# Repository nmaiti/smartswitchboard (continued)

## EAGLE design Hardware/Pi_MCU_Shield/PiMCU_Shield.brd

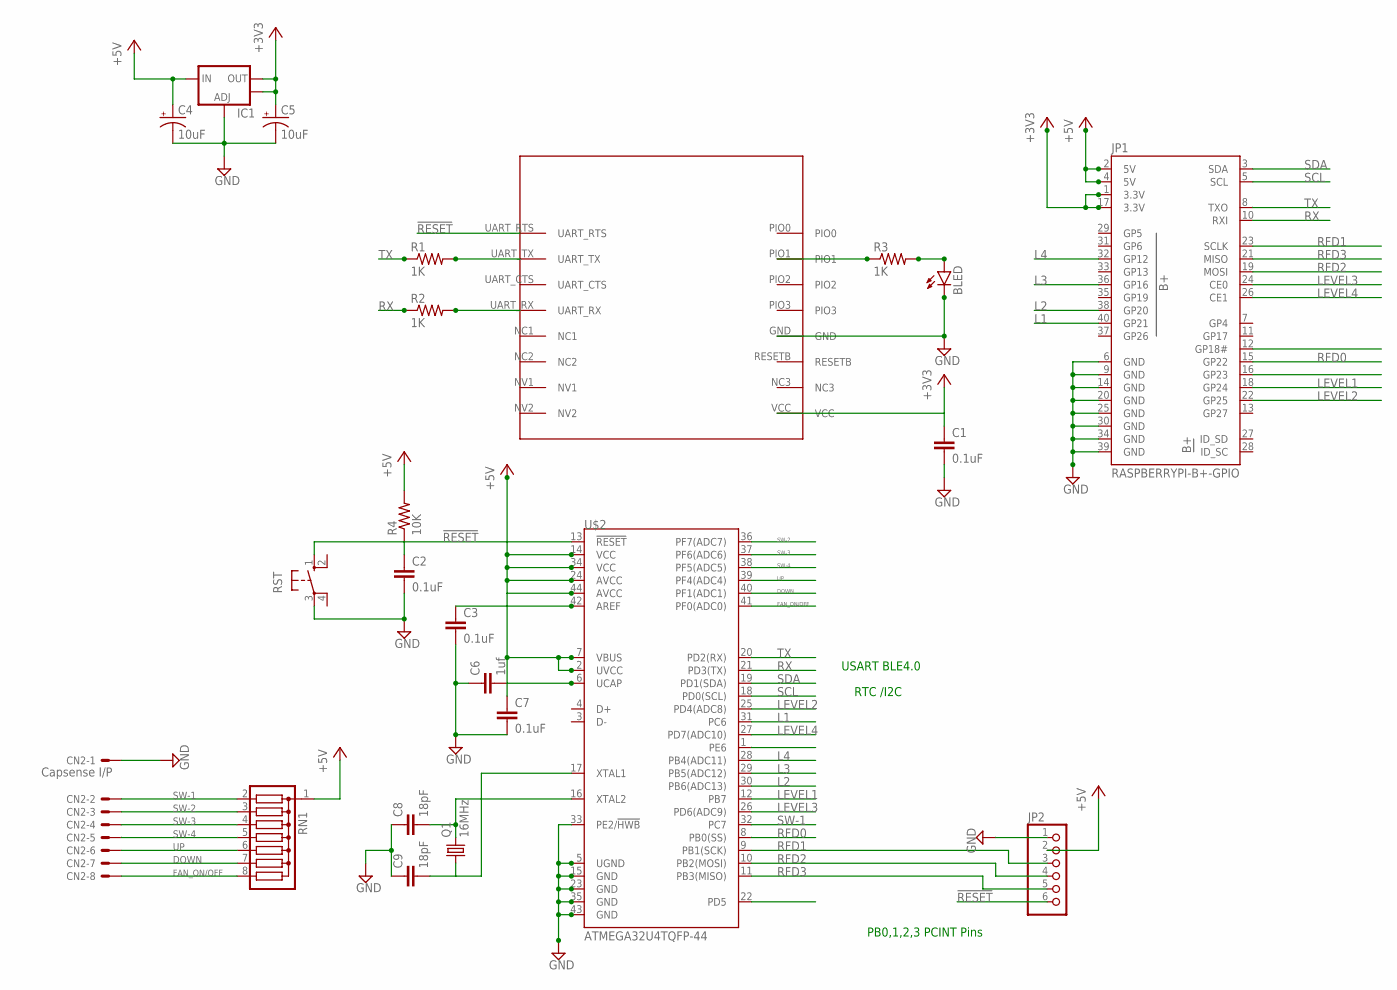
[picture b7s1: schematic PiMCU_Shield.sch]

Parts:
BLED: LED1206; LED-1206
C1, C2, C3, C7: 0.1uF; 1206
C4, C5: 10uF; EIA3216
C6: 1uf; 1206
C8, C9: 18pF; 1206
CN2: Capsense I/P; 22-23-2081
IC1: V_REG_LM1117SOT223; SOT223
JP1: RASPBERRYPI-B+-GPIO; 2X20-SHROUDED
JP2: PINHD-1X6; 1X06
Q1: 16MHz; HC49UP
R1, R2, R3: 1K; 1206
R4: 10K; 1206
RN1: G07R; SIL8
RST: 10-XX; B3F-10XX
U$1: HM-11
U$2: ATMEGA32U4TQFP-44; TQFP44

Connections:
!RESET: C2.1, JP2.6, R4.1, RST.1 (S), U$1.UART_RTS, U$2.13 (!RESET)
+3V3: C1.1, C5.A (+), IC1.2 (OUT), IC1.4 (OUT), JP1.1 (3.3V), JP1.17 (3.3V), U$1.VCC
+5V: C4.A (+), C7.1, IC1.3 (IN), JP1.2 (5V), JP1.4 (5V), JP2.2, R4.2, RN1.1, U$2.2 (UVCC), U$2.7 (VBUS), U$2.14 (VCC), U$2.24 (AVCC), U$2.34 (VCC), U$2.44 (AVCC)
DOWN: CN2.7, RN1.7, U$2.40 (PF1(ADC1))
FAN_ON/OFF: CN2.8, RN1.8, U$2.41 (PF0(ADC0))
GND: BLED.C, C1.2, C2.2, C3.2, C4.C (-), C5.C (-), C6.1, C7.2, C8.1, C9.1, CN2.1, IC1.1 (ADJ), JP1.6 (GND), JP1.9 (GND), JP1.14 (GND), JP1.20 (GND), JP1.25 (GND), JP1.30 (GND), JP1.34 (GND), JP1.39 (GND), JP2.1, RST.3, U$1.GND, U$2.5 (UGND), U$2.15 (GND), U$2.23 (GND), U$2.33 (PE2/!HWB), U$2.35 (GND), U$2.43 (GND)
L1: JP1.40 (GP21), U$2.31 (PC6)
L2: JP1.38 (GP20), U$2.30 (PB6(ADC13))
L3: JP1.36 (GP16), U$2.29 (PB5(ADC12))
L4: JP1.32 (GP12), U$2.28 (PB4(ADC11))
LEVEL1: JP1.18 (GP24), U$2.12 (PB7)
LEVEL2: JP1.22 (GP25), U$2.25 (PD4(ADC8))
LEVEL3: JP1.24 (CE0), U$2.26 (PD6(ADC9))
LEVEL4: JP1.26 (CE1), U$2.27 (PD7(ADC10))
unnamed: R1.2, U$1.UART_TX
unnamed: R2.2, U$1.UART_RX
unnamed: R3.1, U$1.PIO1
unnamed: BLED.A, R3.2
unnamed: C3.1, U$2.42 (AREF)
unnamed: C6.2, U$2.6 (UCAP)
unnamed: C8.2, Q1.2, U$2.16 (XTAL2)
unnamed: C9.2, Q1.1, U$2.17 (XTAL1)
RFD0: JP1.15 (GP22), U$2.8 (PB0(SS))
RFD1: JP1.23 (SCLK), JP2.3, U$2.9 (PB1(SCK))
RFD2: JP1.19 (MOSI), JP2.4, U$2.10 (PB2(MOSI))
RFD3: JP1.21 (MISO), JP2.5, U$2.11 (PB3(MISO))
RX: JP1.10 (RXI), R2.1, U$2.21 (PD3(TX))
SCL: JP1.5 (SCL), U$2.18 (PD0(SCL))
SDA: JP1.3 (SDA), U$2.19 (PD1(SDA))
SW-1: CN2.2, RN1.2, U$2.32 (PC7)
SW-2: CN2.3, RN1.3, U$2.36 (PF7(ADC7))
SW-3: CN2.4, RN1.4, U$2.37 (PF6(ADC6))
SW-4: CN2.5, RN1.5, U$2.38 (PF5(ADC5))
TX: JP1.8 (TXO), R1.1, U$2.20 (PD2(RX))
UP: CN2.6, RN1.6, U$2.39 (PF4(ADC4))

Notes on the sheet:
PB0,1,2,3 PCINT Pins
USART BLE4.0
RTC /I2C

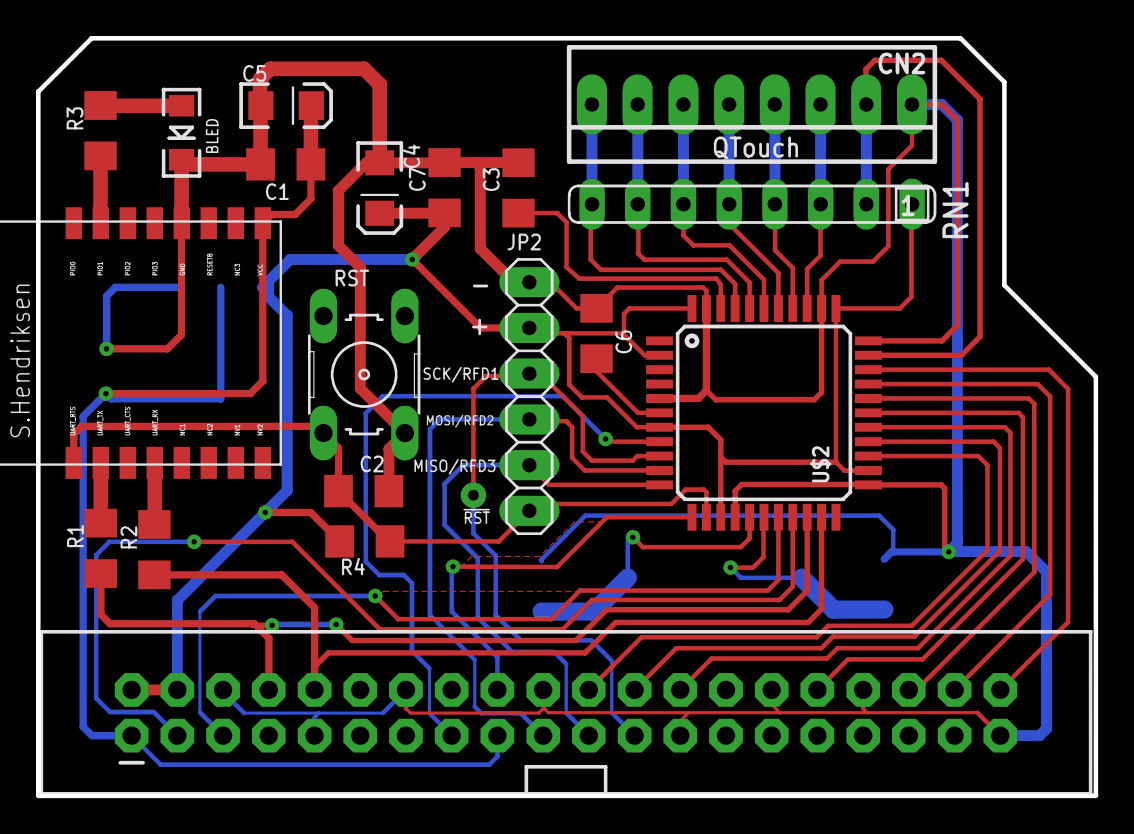
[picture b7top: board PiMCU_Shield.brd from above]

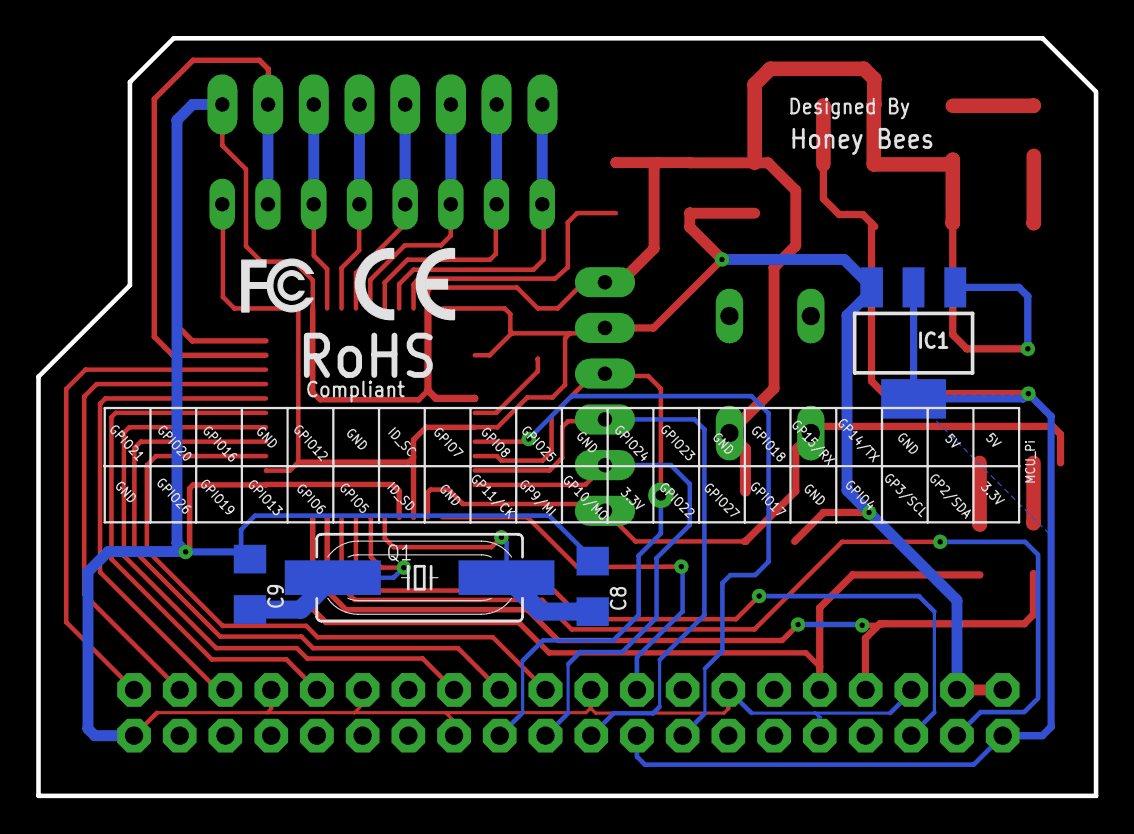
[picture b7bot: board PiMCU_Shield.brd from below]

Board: 2 copper layers, 58.8 x 42.1 mm, 25 parts (4 on the bottom side), 35 nets.

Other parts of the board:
U$4: CE-4MM
U$5: FCC_6.1X15MM

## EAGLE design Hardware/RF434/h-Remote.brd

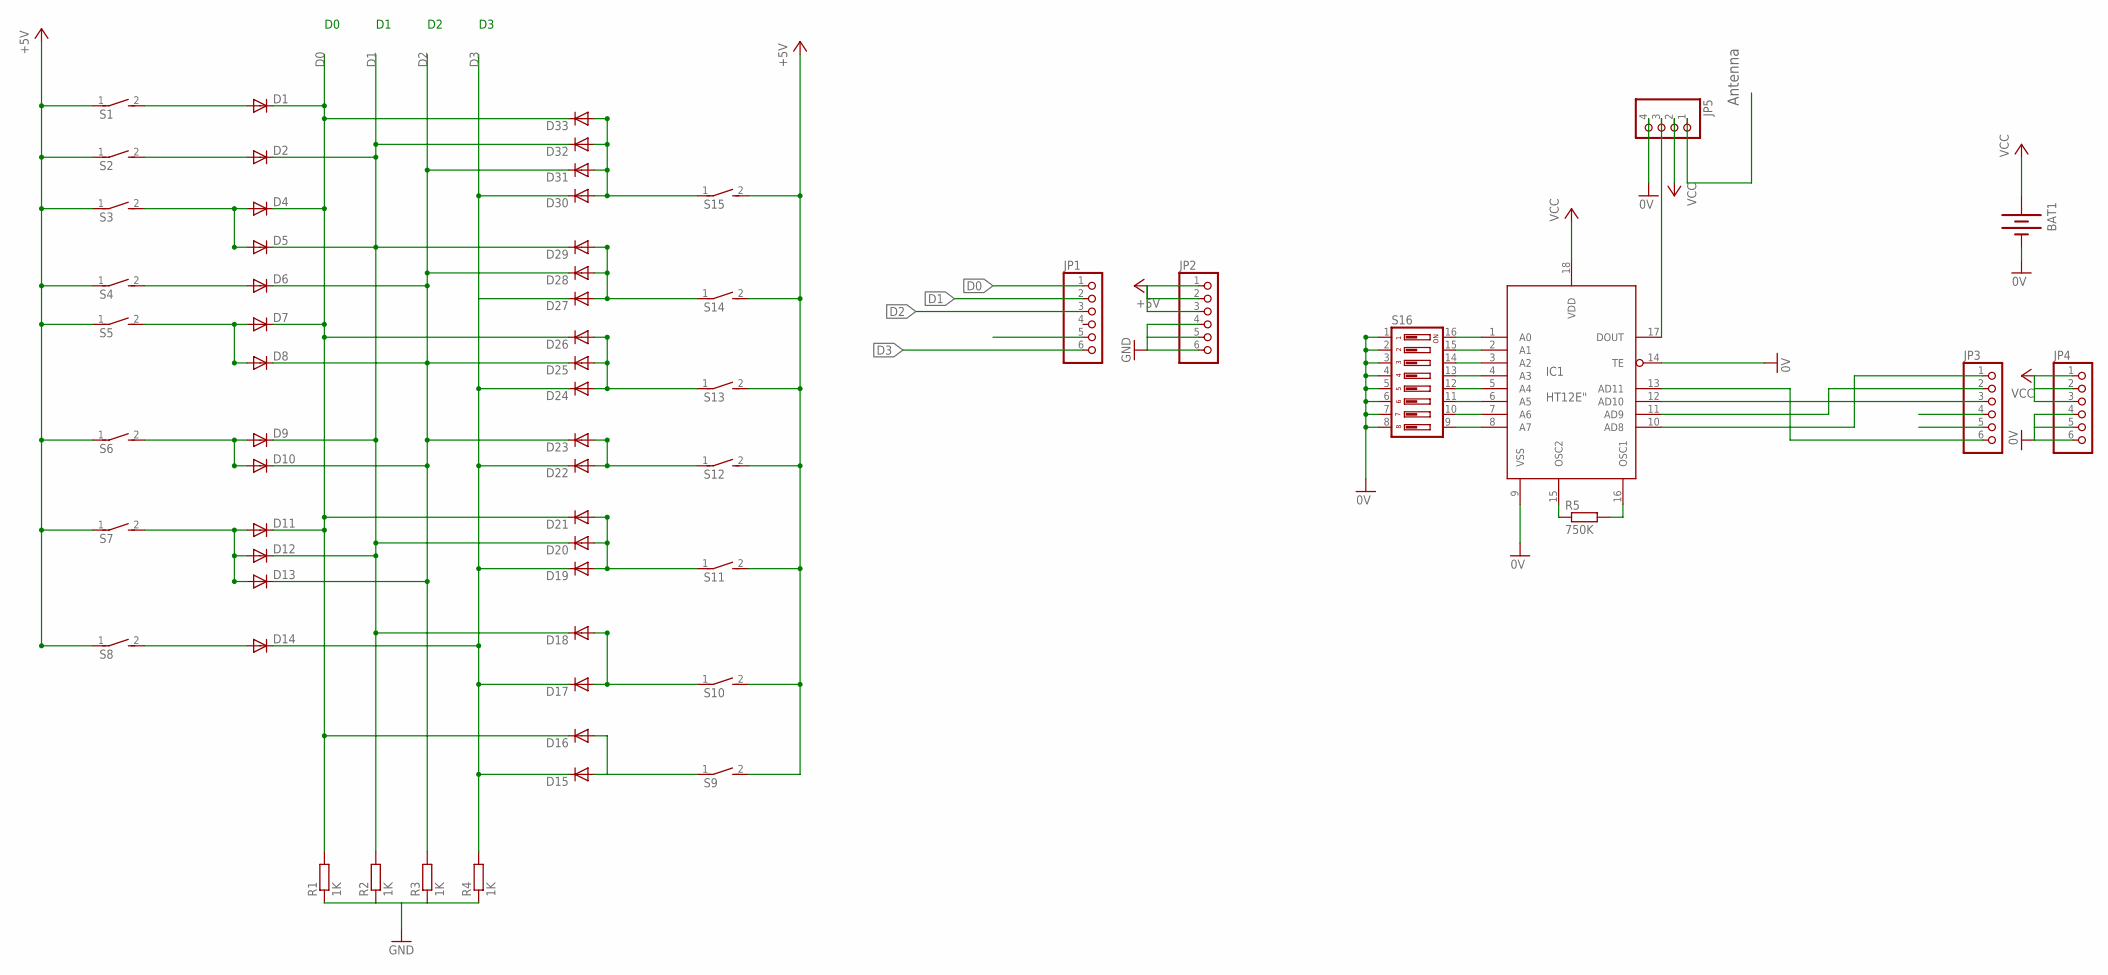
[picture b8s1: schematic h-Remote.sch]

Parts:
BAT1: BATTERY20PTH; BATTCOM_20MM_PTH
D1, D2, D4, D5, D6, D7, D8, D9, D10, D11, D12, D13, D14, D15, D16, D17, D18, D19, D20, D21, D22, D23, D24, D25, D26, D27, D28, D29, D30, D31, D32, D33: DIODE-MELF-MLL41; MELF-MLL41
IC1: HT12E"; 18-DIP-A
JP1, JP2, JP3, JP4: PINHD-1X6; 1X06
JP5: PINHD-1X4; 1X04
R1, R2, R3, R4: 1K; R1206
R5: 750K; 0207/10
S1, S2, S3, S4, S5, S6, S7, S8, S9, S10, S11, S12, S13, S14, S15: DS01E; DS-01
S16: DIP08YL

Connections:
0V: BAT1.2 (-), IC1.9 (VSS), IC1.14 (TE), JP4.4, JP4.5, JP4.6, JP5.4, S16.1, S16.2, S16.3, S16.4, S16.5, S16.6, S16.7, S16.8
+5V: JP2.1, JP2.2, JP2.3, S1.1, S2.1, S3.1, S4.1, S5.1, S6.1, S7.1, S8.1, S9.2, S10.2, S11.2, S12.2, S13.2, S14.2, S15.2
D0: D1.C, D4.C, D7.C, D11.C, D16.C, D21.C, D26.C, D33.C, JP1.1, R1.2
D1: D2.C, D5.C, D9.C, D12.C, D18.C, D20.C, D29.C, D32.C, JP1.2, R2.2
D2: D6.C, D8.C, D10.C, D13.C, D23.C, D25.C, D28.C, D31.C, JP1.3, R3.2
D3: D14.C, D15.C, D17.C, D19.C, D22.C, D24.C, D27.C, D30.C, JP1.6, R4.2
GND: JP2.4, JP2.5, JP2.6, R1.1, R2.1, R3.1, R4.1
unnamed: D7.A, D8.A, S5.2
unnamed: IC1.13 (AD11), JP3.6
unnamed: IC1.12 (AD10), JP3.3
unnamed: D2.A, S2.2
unnamed: IC1.11 (AD9), JP3.2
unnamed: D6.A, S4.2
unnamed: D4.A, D5.A, S3.2
unnamed: D1.A, S1.2
unnamed: D9.A, D10.A, S6.2
unnamed: D11.A, D12.A, D13.A, S7.2
unnamed: D14.A, S8.2
unnamed: D15.A, D16.A, S9.1
unnamed: D17.A, D18.A, S10.1
unnamed: D19.A, D20.A, D21.A, S11.1
unnamed: D22.A, D23.A, S12.1
unnamed: D24.A, D25.A, D26.A, S13.1
unnamed: D27.A, D28.A, D29.A, S14.1
unnamed: D30.A, D31.A, D32.A, D33.A, S15.1
unnamed: IC1.10 (AD8), JP3.1
unnamed: IC1.1 (A0), S16.16
unnamed: IC1.2 (A1), S16.15
unnamed: IC1.3 (A2), S16.14
unnamed: IC1.4 (A3), S16.13
unnamed: IC1.5 (A4), S16.12
unnamed: IC1.6 (A5), S16.11
unnamed: IC1.7 (A6), S16.10
unnamed: IC1.8 (A7), S16.9
unnamed: IC1.15 (OSC2), R5.1
unnamed: IC1.16 (OSC1), R5.2
unnamed: IC1.17 (DOUT), JP5.3
VCC: BAT1.1 (+), IC1.18 (VDD), JP4.1, JP4.2, JP4.3, JP5.2

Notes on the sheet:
Antenna

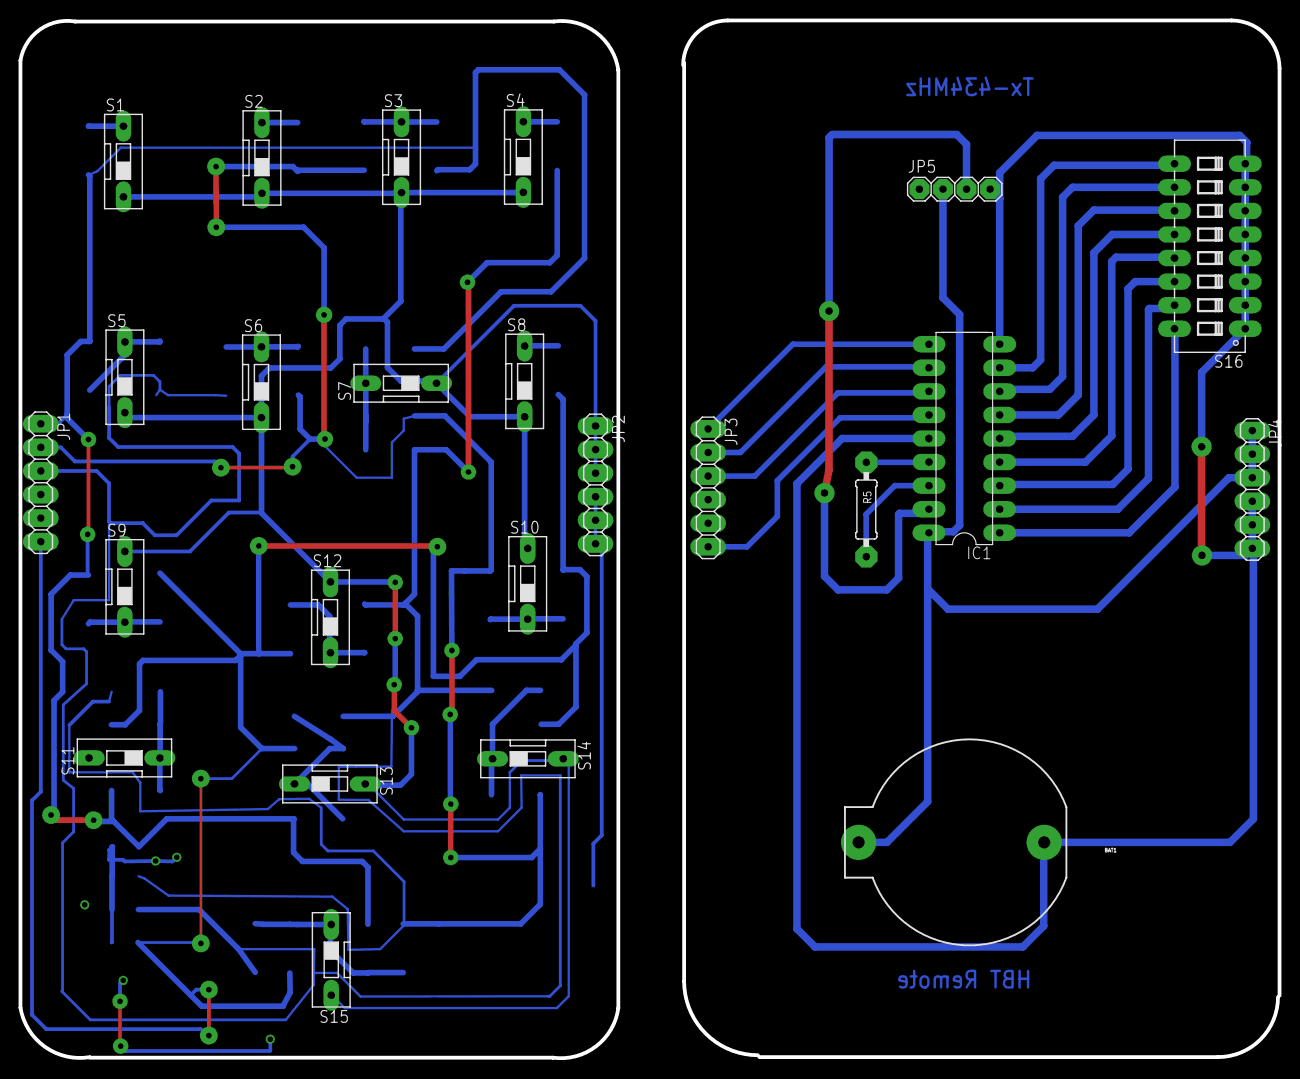
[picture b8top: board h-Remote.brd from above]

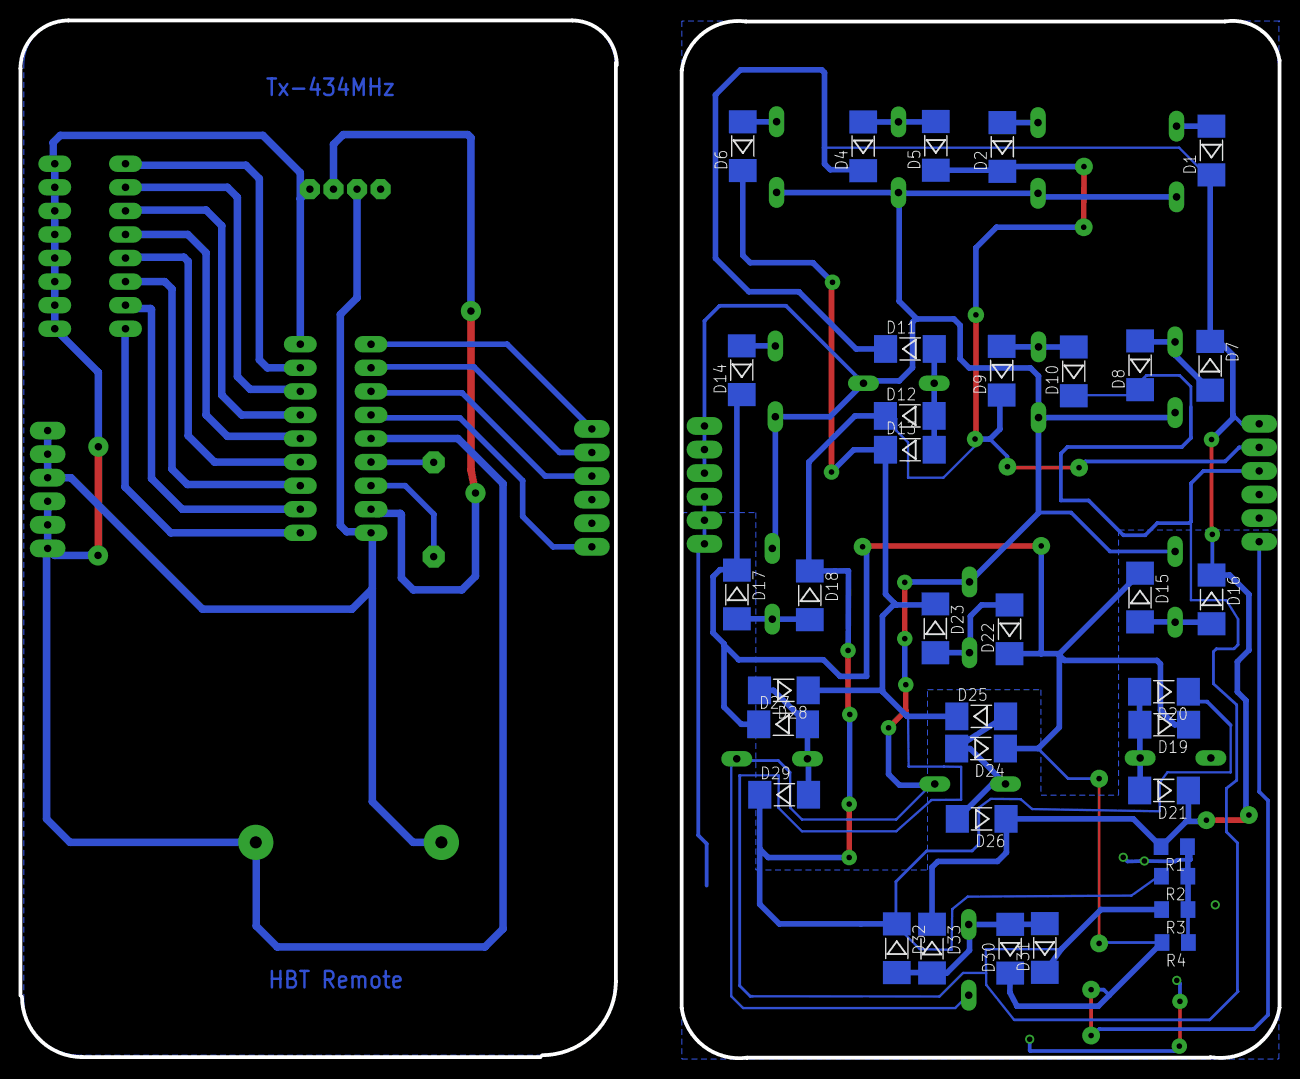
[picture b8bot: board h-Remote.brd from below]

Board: 2 copper layers, 135.7 x 111.8 mm, 60 parts (36 on the bottom side), 38 nets.

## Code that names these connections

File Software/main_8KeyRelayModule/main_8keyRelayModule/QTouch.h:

#ifndef  QTouch_h
#define  QTouch_h

#include <Arduino.h>
#include <HBT.h>
#include "BLE.h"
#include <avr/io.h>


//#define Lamp1_Dir_Input   (DDRD &= 0b0000000)       //PD5 SW1 

//#define SW1   (PIND & 0b00100000)    //PD5
// Capsence Input Pins

#define Lamp1     13  //  ((PINC & 0x80)==0x80)    // PC7   //7    // (PIND & 0b00100000)    //PD5 Input pin             
#define Lamp2     18  // ((PINF & 0x80)==0x80)    //PF7       //4    
#define Lamp3     19  // ((PINF & 0x40)==0x40)    // PF6       //12     //A6 
#define Socket    20  // ((PINF & 0x20)==0x20)    // PF5       //6  
#define Fan_Control 23  //((PINF & 0x01)==0x01)    //PF0        //10     
#define Up          21  //((PINF & 0x10)==0x10)    //PF4        //8
#define Down        22  //((PINF & 0x02)==0x02)     //PF1          //9

// RF Inputs
/// RF Modules Output pins as Input to MCU PB0 - PB3

#define RFD0  14    //D14
#define RFD1  16    //D16(RFD2)
#define RFD2  17    //D17(RFD3)
#define RFD3  15    //D15(RFD1)

//Output Pins to control Triac Switching

#define Load1   5      //5  //  14   //Relay 1 
#define Load2   10      //PB6    //15    //Relay 2
#define Load3   9      //PB5    //16   //Relay 3
#define Load4   8      //PB4      //17   //D17 Relay 4 - Socket pin
#define Level1  11      //5      //D5
#define Level2  4        //13   //D13
#define Level3  12      //18    //D18
#define Level4  6        //19   //D19



class QTouch
{
  
  public:
  
  uint8_t i;
  QTouch();        //Constructor
  void gpioInit(void);
  byte readCapsense(void);
  byte readLoadstatus(void);
  byte readRF(void);
  void cap_setLoad(byte loadValue);
  void L1_ON(void);
  void L2_ON(void);
  void L3_ON(void);
  void Socket_ON(void);
  void FAN_ON(void);             
  void Level2_ON(void);
  void Level3_ON(void);
  void Level4_ON(void);
  void Master_ON(void);
  
  void L1_OFF(void);
  void L2_OFF(void);
  void L3_OFF(void);
  void Socket_OFF(void);
  void FAN_OFF(void);
  void Level2_OFF(void);
  void Level3_OFF(void);
  void Level4_OFF(void);
  void Master_OFF(void);

  void LightControl(uint8_t pinNo , uint8_t pinValue);
  
  
  private:
  
  byte curr_status, prev_status;
  
  uint8_t m_loadValue, pin_num,pin_Value;
  uint8_t prev_loadValue;
  
  
};

#endif

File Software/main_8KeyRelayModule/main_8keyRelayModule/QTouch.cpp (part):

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void QTouch::gpioInit(void)
{
   uint8_t capsensepins[8] = {Lamp1,Lamp2,Lamp3,Socket,Fan_Control,Up,Down};
   uint8_t loadoutpins[8] = {Load1,Load2,Load3,Load4,Level1,Level2,Level3,Level4};//Load6=NC
   
  //Set Pinmodes of I/O pins

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    pinMode(loadoutpins[i],OUTPUT);
  }

   pinMode(RFD0,INPUT);
   pinMode(RFD1,INPUT);
   pinMode(RFD2,INPUT);
   pinMode(RFD3,INPUT);

   digitalWrite(RFD0,LOW);
   digitalWrite(RFD1,LOW);
   digitalWrite(RFD2,LOW);
   digitalWrite(RFD2,LOW);
 /* 
  DDRC = _BV(PC6);       // set output 
  DDRB = _BV(PB6);       // set output
  DDRB = _BV(PB5);       // set output
  DDRB = _BV(PB4);       // set output
  DDRB = _BV(PB7);       // set output
  DDRD = _BV(PD4);       // set output
  DDRD = _BV(PD6);       // set output
  DDRD = _BV(PD7);       // set output
  

  
  PORTC &= ~ _BV(PC6);  //Lamp 1
  PORTB &= ~ _BV(PB6);  // Lamp 2
  PORTB &= ~ _BV(PB5);  //Lamp 3
  PORTB &= ~ _BV(PB4);  //Socket
  PORTB &= ~ _BV(PB7);    //Level 1 OFF
  PORTD &= ~ _BV(PD4);    //Level 2 OFF
  PORTD &= ~ _BV(PD6);    //Level 3 OFF
  PORTD &= ~ _BV(PD7);    //Level 4 OFF
  */
  //Set pinValue to LOW
  /*digitalWrite(Lamp1,LOW);
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
void QTouch::L1_ON(void)  
{
  PORTC |= _BV(PC6);
  //digitalWrite(Load1,HIGH);
  Serial.println("Lamp 1 ON");
}

void QTouch::L2_ON(void)
{
  PORTB |= _BV(PB6);
  //digitalWrite(Load2,HIGH);
  Serial.println("Lamp 2 ON");
}

void QTouch::L3_ON(void)
{
  PORTB |= _BV(PB5);
  //digitalWrite(Load3,HIGH);
  Serial.println("Lamp 3 ON"); 
}

void QTouch::Socket_ON(void)      //Socket Control SW
{
  PORTB |= _BV(PB4);
  //digitalWrite(Load4,HIGH);
  Serial.println("Socket ON");
}
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  //digitalWrite(Level1,HIGH);    //set to Level-1
  //Level2_OFF();Level3_OFF();Level4_OFF();
  
  PORTB |= _BV(PB7);    //Level1 ON
  PORTD &= ~ _BV(PD4);    //Level 2 OFF
  PORTD &= ~ _BV(PD6);    //Level 3 OFF
  PORTD &= ~ _BV(PD7);    //Level 4 OFF
  
}

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{
  //digitalWrite(Level2,HIGH);
  
  PORTD |= _BV(PD4);    //Level 2 ON
  Level3_OFF();Level4_OFF();
  digitalWrite(Level1,LOW);
 
  //PORTB &= (0<<PB7);    //Level 1 OFF
  //PORTD &= (0<<PD6);    //Level 3 OFF
  //PORTD &= (0<<PD7);    //Level 4 OFF
 
}

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{
  //digitalWrite(Level3,HIGH);
  
  PORTD |= _BV(PD6);    //Leevel 3 ON
  digitalWrite(Level1,LOW);
  Level2_OFF();Level4_OFF();
  
  //PORTB &= (0<<PB7);    //Level 1 OFF
  //PORTD &= (0<<PD4);    //Level 2 OFF
  //PORTD &= (0<<PD7);    //Level 4 OFF
 
}

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{
  //digitalWrite(Level4,HIGH);
  
  PORTD |= _BV(PD7);    //Level 4 ON
  digitalWrite(Level1,LOW);
  Level2_OFF();Level3_OFF();
  
  //PORTB &= (0<<PB7);    //Level 1 OFF
  //PORTD &= (0<<PD4);    //Level 2 OFF
  //PORTD &= (0<<PD6);    //Level 3 OFF
 
}

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  //digitalWrite(Load3,HIGH);
  //digitalWrite(Load4,HIGH);  //Make them OFF
  //Socket_ON();
  //PORTC |= _BV(PC6);    //Load 1 ON
  PORTB |= _BV(PB6);    //Load 2 ON
  PORTB |= _BV(PB5);    //Load 3 ON
  PORTB |= _BV(PB4);    //Load 4 ON
  FAN_ON();                  //Fan at Default Speed Level -1
}
/*========================================================================================================
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
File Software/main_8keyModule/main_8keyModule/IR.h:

#ifndef  IR_h
#define  IR_h

#include <Arduino.h>
#include <TAH.h>
#include "QTouch.h"

#define  FAN    0x1FE58A7
#define  UP     0x1FE609F
#define  DOWN   0x1FEA05F
#define  Master 0x1FE48B7
#define  zero   0x1FEE01F
#define  one    0x1FE50AF
#define  two    0x1FED827
#define  three  0x1FEF807
#define  four   0x1FE30CF
#define  five   0x1FEB04F
#define  six    0x1FE708F
#define  seven  0x1FE00FF
#define  eight  0x1FEF00F
#define  nine   0x1FE9867

//Fan Speed Levels 
#define Level_1  1
#define Level_2  2
#define Level_3  3
#define Level_4  4




class IR
{
  
  public:
  
  int i;
  IR();        //constructor
  //unsigned int readIRSignal(unsigned long int decodedvalue);
  void ir_setLoad(unsigned long int number);
  void FanSpeedControl(byte level);

  
  private:
  
  //unsigned long int curr_decodedvalue;
  //unsigned long int prev_decodedvalue;
  unsigned long int curr_number;
  unsigned long int prev_number;
  
};

#endif
  
  
  

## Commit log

2015-05-01 Added protype of Capsense Eagle Board files
2015-07-10 Added New Hardware and Firmware files
2015-07-10 Deleted test~ file
2015-07-15 updated all .cpp and .ino program files
2015-07-25 Updated Hardware Design files with Fan regulator and Power supply cct.
2015-08-05 Updated BOM
2015-08-11 updated the Hardware files
2015-09-30 Updated the Hardware and software drives
2015-10-31 Updated the Hardware and software files
2015-12-22 Updated the Hardware Files with Vr2
2016-01-11 Updated with Vr2 of Switchboard
2016-01-29 Updated with 8 Module Relay Board Design
2016-02-09 Updated with 8keyRelayModule firmware files
2016-02-23 Updated the Relay module firmware
2016-08-02 Created Rpi Compatible MCU board
2016-08-02 Modified 8ModuleBoard_vr2 files
2016-08-02 changes saved to main_8keyModule.ino file
2016-08-02 modified code with embedded C and work in progress
2016-08-02 Added HM-11 FCC CE Certifications
2016-08-02 Added SMPS hardware and Gerber details
2016-08-02 Added Drill file
2016-08-02 Added Report files
2016-08-02 Added Proto Board Design files
2016-08-19 updated with latest changes in hardware and software files
2016-08-25 Added RF support in software
2016-08-25 Included HBT library support
2016-08-30 implemented logic for RF Remote controller
2016-08-30 Included HBT library
2016-08-30 sync all software and hardware files
2016-12-16 included HBT.cpp library file
2016-12-16 Included HBT.h library file
2016-12-16 generated board pdf file
2016-12-16 modified BOM file
2016-12-16 included SMPS gerber files
2016-12-16 updated gerber data of Pi_MCU_backend board
2016-12-16 modified .h file
2016-12-16 modified file
2016-12-16 modified .brd file
2016-12-16 modified .sch file
2016-12-16 included .pdf file
2016-12-16 removed case(555): ble on connect response code , no need to implemnt it
2016-12-16 removed .b## and .s## files generated
